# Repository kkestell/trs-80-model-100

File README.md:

# TRS-80 Model 100

## Overview

TODO

TODO

## Screen

### LCD

The display has a 1920×480 IPS panel. I think I read somewhere that these were designed as rear-view mirrors. At 218mm, it's actually a little wider than the original LCD.

### Bracket

The LCD is mounted to a custom 3D printed bracket that's attached to the enclosure using the original screw bosses. The LCD fits snugly between bracket and the front plastic, with three pieces of double sided tape between the display and the bracket for good measure.

### Configuration

```ini
hdmi_force_hotplug=1
hdmi_group=2
hdmi_mode=87
hdmi_force_mode=1
hdmi_timings=480 0 30 30 30 1920 0 6 6 6 0 0 0 60 0 66000000 7
max_framebuffer_width=480
max_framebuffer_height=1920
display_hdmi_rotate=1
```

## Keyboard

### Matrix

The TRS-80 keyboard matrix is 9 columns by 8 rows. The pins on the keyboard PCB are labeled 1-20. Pins 1-9 correspond to columns 0-8, pins 10 and 11 aren't used, pins 12-19 correspond to rows 0-7, and pin 20 is ground.

#### Wiring

| Keyboard Pin | Function |
|--------------|----------|
| 1            | Column 0 |
| 2            | Column 1 |
| 3            | Column 2 |
| 4            | Column 3 |
| 5            | Column 4 |
| 6            | Column 5 |
| 7            | Column 6 |
| 8            | Column 7 |
| 9            | Column 8 |
| 10           | Unused   |
| 11           | Unused   |
| 12           | Row 0    |
| 13           | Row 1    |
| 14           | Row 2    |
| 15           | Row 3    |
| 16           | Row 4    |
| 17           | Row 5    |
| 18           | Row 6    |
| 19           | Row 7    |
| 20           | GND      |

#### Scanning

The basic process for scanning the keyboard matrix is:

```
INITIALIZE all columns as OUTPUT and set HIGH
INITIALIZE all rows as INPUT with internal pull-up resistors

FOR each column FROM 0 TO num_cols - 1 DO
    SET the current column TO LOW
    
    FOR each row FROM 0 TO num_rows - 1 DO
        IF the value at the current row IS LOW THEN
            key at the current position (row, column) is being pressed
        END IF
    ENDFOR

    SET the current column TO HIGH
ENDFOR
```

### Firmware v1

For this first experiment, I connected the rows and columns directly to the digital I/O pins on an Arduino Pro Micro. The firmware scans the rows and columns every 5ms, and uses the `Keyboard` library to send key presses and releases to the host.

#### Wiring

| Keyboard Pin | Function | Arduino Pro Micro Pin |
|--------------|----------|-----------------------|
| 1            | Column 0 | 0                     |
| 2            | Column 1 | 1                     |
| 3            | Column 2 | 2                     |
| 4            | Column 3 | 3                     |
| 5            | Column 4 | 4                     |
| 6            | Column 5 | 5                     |
| 7            | Column 6 | 6                     |
| 8            | Column 7 | 7                     |
| 9            | Column 8 | 8                     |
| 10           | Unused   |                       |
| 11           | Unused   |                       |
| 12           | Row 0    | 21                    |
| 13           | Row 1    | 20                    |
| 14           | Row 2    | 19                    |
| 15           | Row 3    | 18                    |
| 16           | Row 4    | 15                    |
| 17           | Row 5    | 14                    |
| 18           | Row 6    | 16                    |
| 19           | Row 7    | 10                    |
| 20           | GND      | GND                   |

#### Code

```arduino
#define USE_TIMER_3 true

#include <TimerInterrupt.h>
#include <ISR_Timer.h>

#include <Keyboard.h>

#define TIMER_INTERVAL_MS 5

#define num_cols 9
#define num_rows 8

int cols[num_cols] = { 0,  1,  2,  3,  4,  5,  6,  7, 8};
int rows[num_rows] = {21, 20, 19, 18, 15, 14, 16, 10   };

char charmap[72] = {
    /*      0    1    2    3     4    5                6              7       8 */
    /* 0 */ 'z', 'a', 'q', 'o',  '1', '9',             ' ',           KEY_F1, KEY_LEFT_SHIFT,
    /* 1 */ 'x', 's', 'w', 'p',  '2', '0',             KEY_BACKSPACE, KEY_F2, KEY_LEFT_CTRL,
    /* 2 */ 'c', 'd', 'e', ']',  '3', '-',             ' ',           KEY_F3, ' ',
    /* 3 */ 'v', 'f', 'r', ';',  '4', '=',             KEY_ESC,       KEY_F4, ' ',
    /* 4 */ 'b', 'g', 't', '\'', '5', KEY_DOWN_ARROW,  ' ',           KEY_F5, ' ',
    /* 5 */ 'n', 'h', 'y', ',',  '6', KEY_UP_ARROW,    ' ',           KEY_F6, ' ',
    /* 6 */ 'm', 'j', 'u', '.',  '7', KEY_LEFT_ARROW,  ' ',           KEY_F7, ' ',
    /* 7 */ 'l', 'k', 'i', '/',  '8', KEY_RIGHT_ARROW, KEY_RETURN,    KEY_F8, ' ',
};

void timerHandler(void)
{
    static int last_keys[num_rows * num_cols] = { 0 };
    static int next_keys[num_rows * num_cols] = { 0 };

    for (int c = 0; c < num_cols; c++)
    {
        digitalWrite(cols[c], LOW);

        for (int r = 0; r < num_rows; r++)
        {
            if (digitalRead(rows[r]) == LOW)
            {
                int idx = r * num_cols + c;
                next_keys[idx] = 1;
                Serial.print(r);
                Serial.print(",");
                Serial.print(c);
                Serial.print("\n");
            }
        }

        digitalWrite(cols[c], HIGH);
    }

    for (int i = 0; i < num_rows * num_cols; i++)
    {
        char key = charmap[i];

        // press if key is held down for two frames
        if (next_keys[i] && last_keys[i])
        {
            Keyboard.press(key);
        }
        
        // release
        else if (!next_keys[i] && last_keys[i])
        {
            Keyboard.release(key);
        }

        last_keys[i] = next_keys[i];
        next_keys[i] = 0;
    }
}

void setup()
{
    // initialize keyboard library
    Keyboard.begin();

    // pull all columns high
    for (int i = 0; i < num_cols; i++)
    {
        pinMode(cols[i], OUTPUT);
        digitalWrite(cols[i], HIGH);
    }

    // enable internal pull-up for all rows
    for (int i = 0; i < num_rows; i++)
    {
        pinMode(rows[i], INPUT_PULLUP);
    }

    ITimer3.init();
    ITimer3.attachInterruptInterval(TIMER_INTERVAL_MS, timerHandler);
}

void loop()
{
}
```

### Detour: Shift Register Experiments

The easiest way to reduce the number of digital I/O pins used by the keyboard firmware is to use a shift register. Shift registers are either serial-in, parallel-out (SIPO) or parallel-in, serial-out (PISO). We'll need both types to read and write to the keyboard matrix.

#### Serial-In, Parallel-Out ([74HC595](https://www.ti.com/lit/ds/symlink/sn74hc595.pdf))

The 74HC595 is an 8-bit serial-in, parallel-out shift register. This allows us to write to eight outputs using only three digital I/O pins.

```cpp
int latchPin = 8;  // Pin connected to RCLK  (pin 12)
int clockPin = 14; // Pin connected to SRCLK (pin 11)
int dataPin  = 16; // Pin connected to SER   (pin 14)

// NOTE: Also connect VCC (pin 16) to 5V and GND (pin 8) to GND as well as OE (pin 13) to GND.
// If you don't connect OE to GND, the 74HC595 will behave strangely.

void setup()
{
    // Set pins to output so you can control the shift register
    pinMode(latchPin, OUTPUT);
    pinMode(clockPin, OUTPUT);
    pinMode(dataPin,  OUTPUT);
}

void loop()
{
    // Count from 0 to 255, displaying each number in binary on eight LEDs
    for (int num = 0; num < 256; num++)
    {
        // Take the latch pin low so the LEDs don't change while you're sending in bits
        digitalWrite(latchPin, LOW);

        // Shift out the bits
        shiftOut(dataPin, clockPin, MSBFIRST, num);

        // Take the latch pin high so the LEDs will light up
        digitalWrite(latchPin, HIGH);

        delay(50);
    }
}
```

This covers writing to the shift register, but we still need to read from the keyboard.

#### Parallel-In, Serial-Out ([74HC165](https://www.ti.com/lit/ds/symlink/sn74hc165.pdf))

The 74HC165 is an 8-bit parallel-in, serial-out shift register. This allows us to read eight inputs using only three digital I/O pins.

```cpp
int loadPin  = 8;  // pin connected to SH/LD (pin 1)
int clockPin = 14; // pin connected to CLK   (pin 2)
int dataPin  = 16; // pin connected to QH    (pin 9)

void setup()
{
    // Set the load and clock pins to output so you can control the shift register
    // and the data pin to input so you can read the serial in
    pinMode(loadPin, OUTPUT);
    pinMode(clockPin, OUTPUT);
    pinMode(dataPin, INPUT);

    // Initialize serial communication
    Serial.begin(9600);
}

void loop()
{
    // Take the parallel load pin low
    digitalWrite(loadPin, LOW);

    // ???
    delayMicroseconds(5);
  
    // Take the parallel load pin high to update the QH pin
    digitalWrite(loadPin, HIGH);
    
    // ???
    delayMicroseconds(5);

    // Shift in the bits
    byte inputs = shiftIn(dataPin, clockPin, MSBFIRST);

    // Print the binary input
    for (int i = 7; i >= 0; i--)
    {
        Serial.print(bitRead(inputs, i));
    }
    Serial.println();

    delay(500);
}
```

### Firmware v2

Scanning the keyboard matrix involves writing to the columns and reading from the rows. We'll use a 74HC165 to read the rows, and chain two 74HC595s together to write to the columns.

```
Serial Data        ---> DS (74HC595 #1)
Clock Input        ---> SH_CP (74HC595 #1) 
                   ---> SH_CP (74HC595 #2)
Latch Input        ---> ST_CP (74HC595 #1) 
                   ---> ST_CP (74HC595 #2)
Q7' (74HC595 #1)   ---> DS (74HC595 #2)
Q0-Q7 (74HC595 #1) ---> Output Bits 1-8
Q0-Q7 (74HC595 #2) ---> Output Bits 9-16
```

TODO

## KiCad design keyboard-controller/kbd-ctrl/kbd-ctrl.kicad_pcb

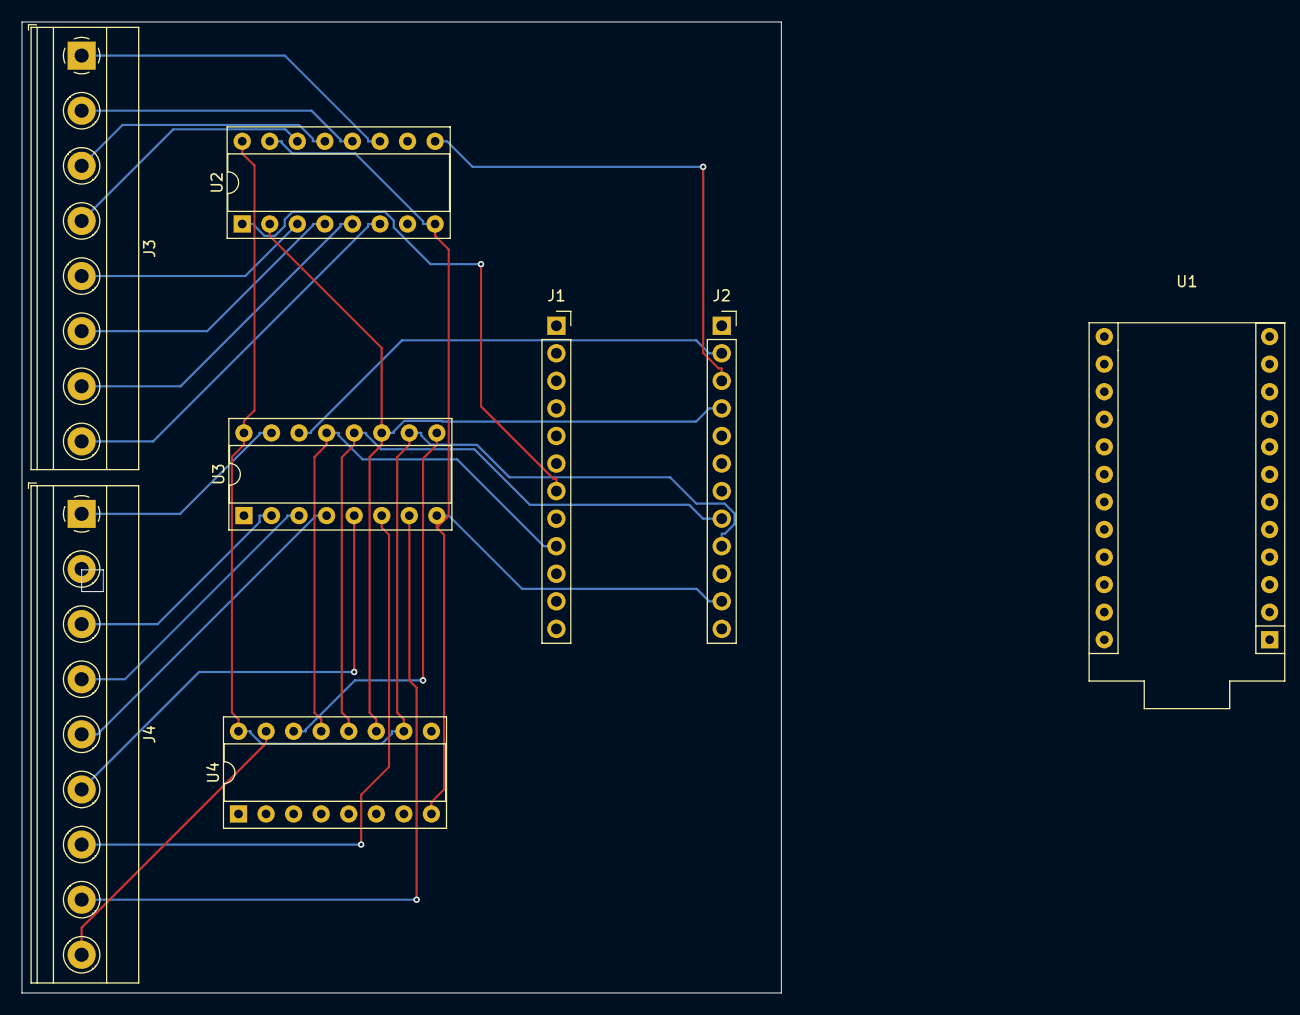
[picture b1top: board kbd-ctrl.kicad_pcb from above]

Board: 2 copper layers, 70.0 x 89.5 mm, 8 parts (0 on the bottom side), 26 nets.

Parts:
J1, J2: Conn_01x12_Socket; PinSocket_1x12_P2.54mm_Vertical
J3: Screw_Terminal_01x08; TerminalBlock_Phoenix_MKDS-1,5-8-5.08_1x08_P5.08mm_Horizont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
J4: Screw_Terminal_01x09; TerminalBlock_Phoenix_MKDS-1,5-9-5.08_1x09_P5.08mm_Horizont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
U1: ProMicro; Sparkfun_Pro_Micro
U2: 74HC165; DIP-16_W7.62mm_Socket
U3, U4: 74HC595; DIP-16_W7.62mm_Socket

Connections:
+5V: J2.9, U2.16 (VCC), U3.10 (~SRCLR), U3.16 (VCC), U4.10 (~SRCLR), U4.16 (VCC)
GND: J2.11, U2.8 (GND), U2.15 (~CE), U3.8 (GND), U4.8 (GND)
unnamed: J1.7, U2.1 (~PL)
unnamed: J1.9, U3.13 (~OE), U4.13 (~OE)
unnamed: J2.2, U3.14 (SER)
unnamed: J2.3, U2.9 (Q7)
unnamed: J2.4, U2.2 (CP), U3.11 (SRCLK), U4.11 (SRCLK)
unnamed: J2.8, U3.12 (RCLK), U4.12 (RCLK)
unnamed: J3.1, U2.11 (D0)
unnamed: J3.2, U2.12 (D1)
unnamed: J3.3, U2.13 (D2)
unnamed: J3.4, U2.14 (D3)
unnamed: J3.5, U2.3 (D4)
unnamed: J3.6, U2.4 (D5)
unnamed: J3.7, U2.5 (D6)
unnamed: J3.8, U2.6 (D7)
unnamed: J4.1, U3.15 (QA)
unnamed: J4.2, U3.1 (QB)
unnamed: J4.3, U3.2 (QC)
unnamed: J4.4, U3.3 (QD)
unnamed: J4.5, U3.4 (QE)
unnamed: J4.6, U3.5 (QF)
unnamed: J4.7, U3.6 (QG)
unnamed: J4.8, U3.7 (QH)
unnamed: J4.9, U4.15 (QA)
unnamed: U3.9 (QH'), U4.14 (SER)

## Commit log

2024-07-27 Add README and images.
